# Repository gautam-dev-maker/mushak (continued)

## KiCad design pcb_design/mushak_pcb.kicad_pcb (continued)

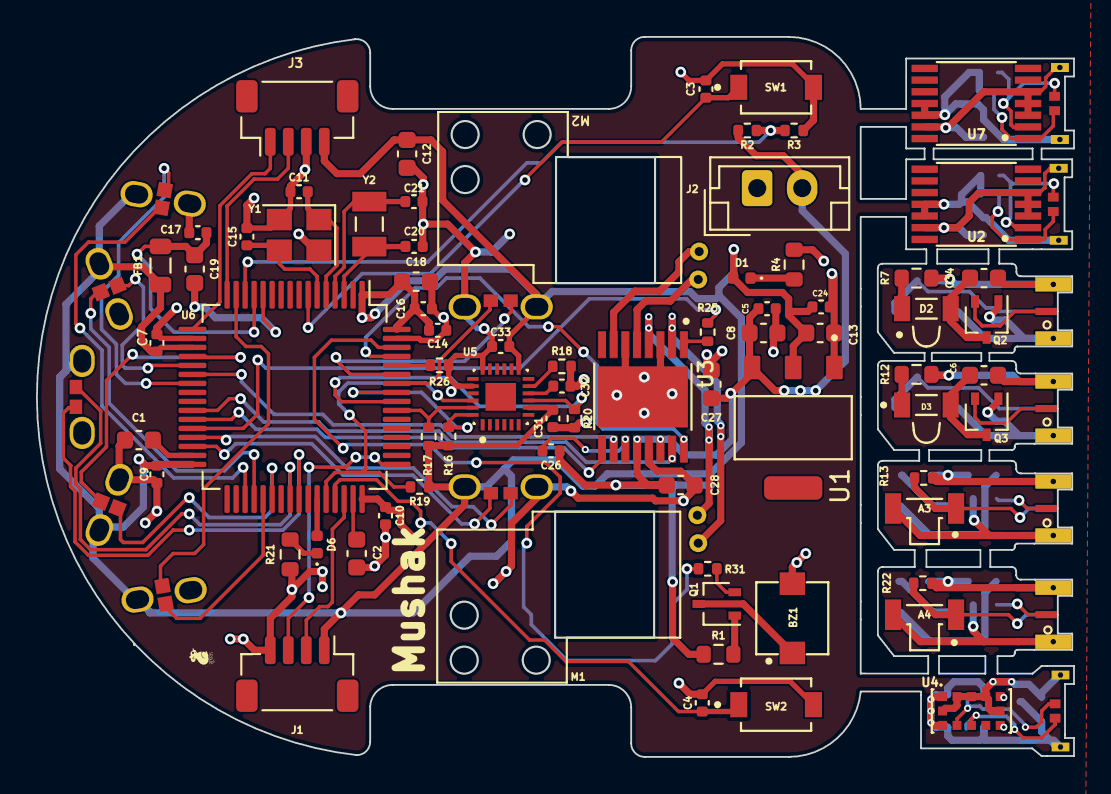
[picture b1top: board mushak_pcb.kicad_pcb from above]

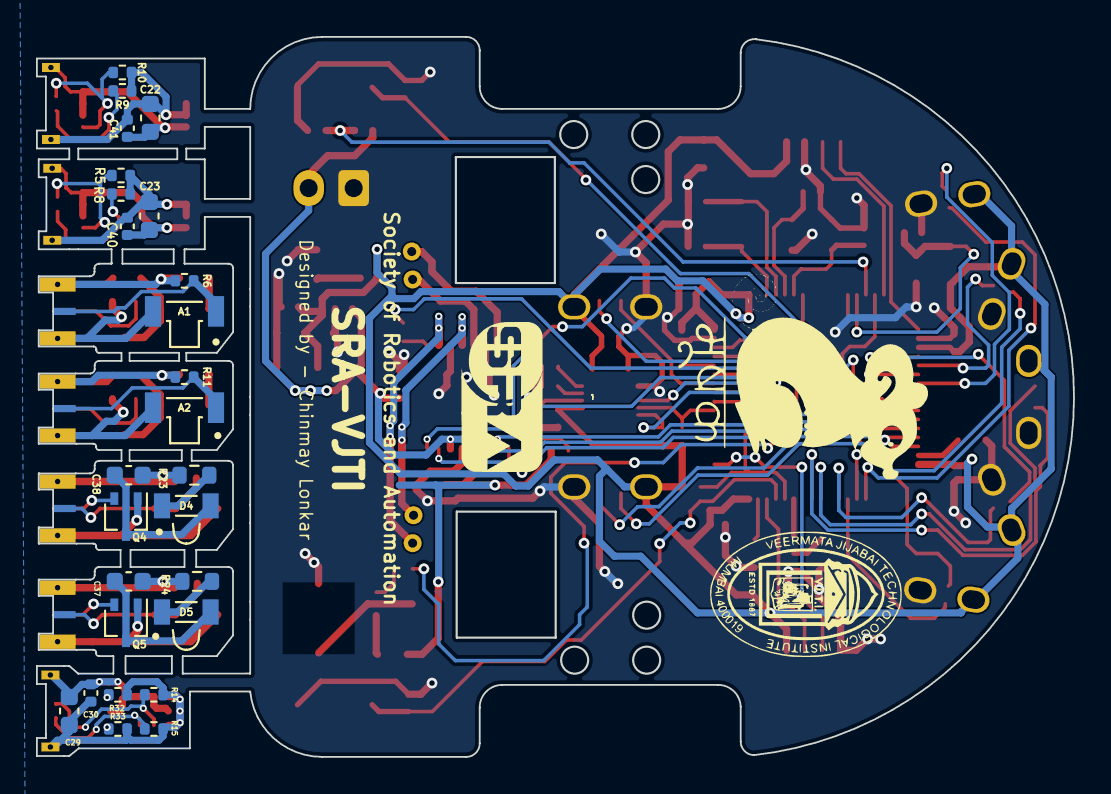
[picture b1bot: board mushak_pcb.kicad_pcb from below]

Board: 2 copper layers, 57.6 x 40.0 mm, 113 parts (27 on the bottom side), 94 nets.

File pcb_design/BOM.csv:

,,,,MUSHAK BILL OF MATERIALS,,,,,,,,,,,,
purchase later,,to purchase ,,,,,,,,,,,,,,
already purchased,,remove from module,,,,,,,,,,,,,,
,,,,,,,f,,,,,,,,,
Ref,Quantity,Value,Comp name,Footprint,Description,Vendor (Digikey),Vendor (Mouser),Indian Vendor (best price),Best Buy (₹ / piece) inc. GST,Cost per build (₹),Purchase Qty,Overall cost (₹) 40% off on Evelta for min. 10 piece,Comments,Cost per build ($),LCSC,Cost ($)
"A1, A2, A3, A4,",4,SFH_3015_FA,SFH_3015_FA,SFH_3015_FA:XDCR_SFH_3015_FA,IR_Reciever,SFH_3015_FA (₹49.86/10piece),SFH_3015_FA (₹40.86/10piece),Not available in India,59.93,239.72,10,498.58,Not available on Indian sites ( Already ordered from semikart),,out of stock,
"BZ1,",1,Buzzer,Buzzer,SMT-0440-T-R:XDCR_SMT-0440-T-R,"Buzzer, polarized",digikey,mouser,semikart(digikey),247.69,247.69,1,247.69,SMD version not available in India,,discontinued,
"C1, C2, C27,",3,2.2uF,C,Capacitor_SMD:C_0603_1608Metric,Unpolarized capacitor,2.2uF_0402 (₹18.46/10piece),2.2uF_0402 (₹11.69/10 piece),evelta,8.26,24.78,10,49.56,0603 package available,0.27,C417153,0.09
"C14, C22, C23,C3, C4, C5, C6, C7, C9, C10, C16, C30, C32, C33, C36, C37, C24, C25",18,0.1uF,C,Capacitor_SMD:C_0402_1005Metric,Unpolarized capacitor,0.1uF_0402 (₹2.32/10piece),0.1uF_0402 (₹3.34/10 piece),evelta,2.12,38.16,35,44.6,pack of 35,0,discontinued,
" C13,",1,22uF,C,Capacitor_SMD:C_0603_1608Metric,Unpolarized capacitor,,,ktron,1.42,1.42,15,21.24,,0,0402 not found,
"C11, C15,",2,20pF (22uF * avaiable),C,Capacitor_SMD:C_0402_1005Metric,Unpolarized capacitor,digikey,20 pF (12.41/10 piece),evelta,3.96,7.92,10,23.76,got 22pF instead of 20pF,0,discontinued,
"C12, C19, C34, C35, C38, C39,",6,1uF,C,Capacitor_SMD:C_0603_1608Metric,Unpolarized capacitor,digikey,mouser,ktron,1,6,20,12,got 0603 package,0.1878,C913450,0.0313
"C17,C31,C26,",3,0.01uF,C,Capacitor_SMD:C_0402_1005Metric,Unpolarized capacitor,digikey,mouser,evelta,0.59,1.77,10,3.54,,0,discontinued,
"C18, C28, C8, C23, C22",5,10uF,C,Capacitor_SMD:C_0603_1608Metric,Unpolarized capacitor,digikey,mouser,evelta,3.54,17.7,10,21.24,got 0603 package,0.556,C703695,0.1112
"C20, C21,",2,12.5pF,C,Capacitor_SMD:C_0402_1005Metric,Unpolarized capacitor,,,evelta,2.5,5,10,15,got 12 pF instead of 12.5pF,0,discontinued,
"C29,",1,4.7uF,C,Capacitor_SMD:C_0603_1608Metric,Unpolarized capacitor,digikey,mouser,evelta,4.72,4.72,10,28.32,got 0603 package,0,discontinued,
"D1, D6,",2,LED,LED,LED_SMD:LED_0402_1005Metric,Light emitting diode,--,--,evelta,3.1,6.2,10,48.97,other colours are cheaper but I went for green,0,,
"D2, D3, D4, D5,",4,SFH_4045N,SFH_4045N,SFH_4045N:LED_SFH_4045N,IR_transmitter,SFH_4045N (₹51.14),SFH_4045N (₹52.47),Not available in India,51.14,204.56,10,337.98,Not available on Indian sites (digikey) ( Already ordered from semikart),0,unavailable,
"FB1,",1,120R,FerriteBead_Small,Inductor_SMD:L_0805_2012Metric,"Ferrite bead, small symbol",,,evelta,2.11,2.11,10,12.66,I want to make sure if this component is correct,0,out of stock,
"IC1, IC2,",2,AS5048B-HTSP,AS5048B-HTSP,AS5048B-HTSP:SOP65P640X120-14N,Magnetic Encoder,digikey,,Not available in India,727.62,1455.24,2,1455.24,we have it already,0,out of stock,
"J1,",1,Conn_01x04_Male,Conn_01x04_Male,Connector_JST:JST_SH_BM04B-SRSS-TB_1x04-1MP_P1.00mm_Vertical,"Generic connector, single row, 01x04",,,evelta,11.8,11.8,0,0,Available in toyo connectors,0,,
"J2,",1,Conn_01x02_Female,Conn_01x02_Female,Connector_JST:JST_EH_B2B-EH-A_1x02_P2.50mm_Vertical,"Generic connector, single row, 01x02",--,--,--,--,--,0,0,Available in toyo connectors,--,--,--
"Q1, Q2, Q3, Q4, Q5,",5,DMN3065LW-7,Q_NMOS_DGS,Package_TO_SOT_SMD:SOT-323_SC-70,"N-MOSFET transistor, drain/gate/source",digikey,,semikart(digikey),42.893,42.893,12,514.72,,0,,
"R1,",1,10E,R,Resistor_SMD:R_0603_1608Metric,Resistor,10 ohm (₹2.4/10 piece),10 ohm (₹1.99/10 piece),evelta,1.89,1.89,5,5.67,,0.075,C153363,0.075
"R4,R21,",2,220E,R,Resistor_SMD:R_0603_1608Metric,Resistor,,,evelta,1.51,3.02,10,9.44,got 0402 package,0,unavailable,
"R5, R8, R9, R10, R14, R15,R2, R3,",8,4.7k,R,Resistor_SMD:R_0402_1005Metric,Resistor,,,evelta,0.47,3.76,20,5.64,got 0603 package,0.3312,C513719,0.0414
"R6, R11, R13, R16, R17, R18, R19, R20, R22, R26",10,10k,R,Resistor_SMD:R_0402_1005Metric,Resistor,,,evelta,1.18,11.8,25,17.7,got 0402 package,0,out of stock,
"R7, R12, R23, R24,",4,100E,R,Resistor_SMD:R_0603_1608Metric,Resistor,,,evelta,1.89,7.56,10,9.44,,0,unavailable,
"R27, R28, R29, R30, R31",5,150E,R,Resistor_SMD:R_0402_1005Metric,Resistor,,,evelta,12,60,10,120,,,,
"SW1, SW2,",2,SW_Push,SW_Push,TL1015AF160QG:SW_TL1015AF160QG,"Push button switch, generic, two pins",,,evelta,2.183,4.366,10,21.83,,0,discontinued,
"U2,",1,BA30BC0FP-E2,BA30BC0FP-E2,IPD50P04P4L-11:DPAK228P998X235-3N,1A 3V LDO,,,semikart(mouser),100.78,100.78,3,302.34,,0,out of stock,
"U3,",1,DRV8833PW,DRV8833PW,Package_SO:TSSOP-16_4.4x5mm_P0.65mm,"Dual H-Bridge Motor Driver, TSSOP-16",digikey,mouser,Not available in India,209.34,209.34,1,209.34,,3.4858,C50506,3.4858
"U4,",1,VL6180XV0NR/1,VL6180XV0NR{slash}1,VL6180XV0NR_1:LGA12R75P2X6_280X480X110,ToF,digikey,mouser,tanotis,648,648,1,648,,3.2063,C2688732,3.2063
"U5,",1,MPU-6500,MPU-6500,MPU-6500:QFN40P300X300X95-25N,IMU,digikey,mouser,Not available in India (from module),727.89,727.89,1,727.89,,3.5651,C50278,3.5651
"U6,",1,STM32F405RGTx,STM32F405RGTx,Package_QFP:LQFP-64_10x10mm_P0.5mm,"ARM Cortex-M4 MCU, 1024KB flash, 128KB RAM, 168MHz, 1.8-3.6V, 51 GPIO, LQFP-64",digikey,mouser,Not available in India,,0,,0,,10.1327,C15742,10.1327
"Y1,",1,25Mhz,Crystal_GND24,Crystal:Crystal_SMD_3225-4Pin_3.2x2.5mm,"Four pin crystal, GND on pins 2 and 4",,,electronicscomp,34.69,34.69,10,208.14,,0.8782,C295525,0.8782
"Y2,",1,32.768kHz,Crystal,ABS07-32:XTAL_ABS07-32.768KHZ-T,Two pin crystal,assign footprint,,evelta,9.44,9.44,3,28.32,,0.1737,C93228,0.1737
Number of SMD components = ,101,,,,,,,,,,,,,,,
,,,,,,,,,,,TOTAL,5648.85,,,,
,98,,,,,,,,,,,,,,,

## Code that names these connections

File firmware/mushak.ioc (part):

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Mcu.Name=STM32F405RGTx
Mcu.Package=LQFP64
Mcu.UserName=STM32F405RGTx
PA0-WKUP.Signal=ADCx_IN0
PA1.Signal=ADCx_IN1
PA10.GPIOParameters=GPIO_Label
PA10.GPIO_Label=DEBUG_LED
PA10.Signal=GPIO_Output
PA11.GPIOParameters=PinState,GPIO_Label
PA11.GPIO_Label=MPU6500_CS
PA11.PinState=GPIO_PIN_RESET
PA11.Signal=GPIO_Output
PA12.GPIOParameters=GPIO_Label
PA12.GPIO_Label=DEBUG_BTN
PA12.Signal=GPIO_Input
PA13.Mode=Serial_Wire
PA13.Signal=SYS_JTMS-SWDIO
PA14.Mode=Serial_Wire
PA14.Signal=SYS_JTCK-SWCLK
PA2.Mode=Asynchronous
PA2.Signal=USART2_TX
PA3.Mode=Asynchronous
PA3.Signal=USART2_RX
PA4.Signal=ADCx_IN4
PA5.Signal=ADCx_IN5
PA6.Signal=S_TIM13_CH1
PA7.Signal=ADCx_IN7
PA8.Mode=I2C
PA8.Signal=I2C3_SCL
PB0.Signal=S_TIM3_CH3
PB1.Signal=S_TIM3_CH4
PB10.Mode=I2C
PB10.Signal=I2C2_SCL
PB11.Mode=I2C
PB11.Signal=I2C2_SDA
PB14.Signal=S_TIM12_CH1
PB15.Signal=S_TIM12_CH2
PB2.GPIOParameters=GPIO_Speed,GPIO_Label
PB2.GPIO_Label=DRV8833_EN
PB2.GPIO_Speed=GPIO_SPEED_FREQ_HIGH
PB2.Signal=GPIO_Output
PB3.Mode=Full_Duplex_Master
PB3.Signal=SPI1_SCK
PB4.Mode=Full_Duplex_Master
PB4.Signal=SPI1_MISO
PB5.Mode=Full_Duplex_Master
PB5.Signal=SPI1_MOSI
PB6.Mode=I2C
PB6.Signal=I2C1_SCL
PB7.Mode=I2C
PB7.Signal=I2C1_SDA
PB8.Signal=S_TIM10_CH1
PB9.Signal=S_TIM11_CH1
PC14-OSC32_IN.Mode=LSE-External-Oscillator
PC14-OSC32_IN.Signal=RCC_OSC32_IN
PC15-OSC32_OUT.Mode=LSE-External-Oscillator
PC15-OSC32_OUT.Signal=RCC_OSC32_OUT
PC6.Signal=S_TIM3_CH1
PC7.Signal=S_TIM3_CH2
PC9.Mode=I2C
PC9.Signal=I2C3_SDA
PH0-OSC_IN.Mode=HSE-External-Oscillator
PH0-OSC_IN.Signal=RCC_OSC_IN
PH1-OSC_OUT.Mode=HSE-External-Oscillator
PH1-OSC_OUT.Signal=RCC_OSC_OUT
RCC.HSE_VALUE=25000000
RCC.SYSCLKFreq_VALUE=168000000
RCC.SYSCLKSource=RCC_SYSCLKSOURCE_PLLCLK
board=custom

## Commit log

2022-07-05 Add gitignore file
2022-07-19 Add BLE logging support
2022-07-19 Add functionality to choose USART instance in BLE logging library
2022-07-19 Add I2C library and VL6180x driver
2022-07-19 Add AS5600 driver
2022-07-20 Correct the typo of i2c in Makefile
2022-07-20 Solve I2C_Handler bug
2022-08-01 vl6180x tested
2022-08-05 update VL6180x driver
2022-08-07 Update VL6180x to give correct readings
2022-08-09 Add MPU6500 driver
2022-08-09 Add schematics
2022-08-09 Add footprints
2022-08-11 Update Schematics and footprints for sensors
2022-08-11 updated .gitignore
2022-08-12 Add Schematic for stm32F405
2022-08-13 Added CAD Files
2022-08-14 changed footprints of capacitors and resistors
2022-08-15 Add DRV8833 driver api
2022-08-15 made draft pcb footprint placement
2022-08-15 Add 3d models to footprint
2022-08-19 updated footprint for motors
2022-08-20 corrected encoder and motor driver schematics
2022-08-20 VL6180x part routed
2022-08-23 changed footprint of passive components
2022-08-23 Started Poer trace routing
2022-08-24 completed routing
2022-08-25 Completed sensor routing
2022-08-26 modified pcb outline and graphics
2022-08-26 modified graphics
2022-08-28 Added the New Mounts
2022-08-28 Updated graphics and added dimensions
2022-08-28 Update README.md to include the firmware part
2022-08-28 PCB Design for Mushak (#2)
    * Add Schematic for stm32F405
    * changed footprints of capacitors and resistors
    * made draft pcb footprint placement
    * Add 3d models to footprint
    * updated footprint for motors
    * corrected encoder and motor driver schematics
2022-08-28 Add PCB images
2022-08-28 Added assets folder for CAD design
2022-08-28 Update README.md
    Created Readme for CAD model
2022-08-29 Add File structure in README.md
2022-08-29 changed oscilattor placement
2022-08-29 Add files via upload
    Added final bot assembly pic
2022-08-29 Update README.md
    Added info to description of parts and final assembly pic
2022-08-29 Add readme and change sensor angles
2022-08-29 Add README for PCB Design
2022-08-29 CHanged angles for IR Sensor placement
2022-08-29 PCB_Readme (#3)
    * Add readme and change sensor angles
    * Add README for PCB Design
    * CHanged angles for IR Sensor placement
2022-08-29 Added New PCB Assembly
2022-08-30 Add images
2022-08-30 renamed folder and add pcb images
2022-08-30 deleted extra folder
2022-08-30 Edited CAD Readme
2022-08-30 correct path for images in README
2022-08-30 Fixed Image issues in ReadME
2022-08-30 Bold the communication protocol in README.md
2022-08-30 Added CAD Design
2022-08-30 Add the CAD Design in README.md
2022-08-30 Improved File Structure
2022-08-30 PCB Design Readme (#4)
    Update PCB Readme.md
2022-08-30 Add gerbers
2022-08-30 add graphiccs on PCB
2022-08-30 Update the pcb notation image
2022-08-30 Correct the discrepancies in README.md
2022-08-30 Add "About the project" above the "Table of Content"
2022-08-31 Add IR placement logic
2022-08-31 Correct IR placement image
2022-08-31 Add schematics pdf to pcb_design folder
2022-09-02 Add BOM to pcb_design
2022-09-14 Add "-u_printf_float" flag in linker script
    This commit solves the floating point issue in BLE_Logger.
    The flag was required to be added as the way to enable FPU for
    complex floating point processing.
2022-09-15 Remove ".lib" from .gitignore
2022-09-15 changed AS5600 to AS5048B
2022-09-15 change capacitor silkscreen placement
2022-09-18 modified capacitors for encoders
2022-09-18 update gerbers
2022-09-22 Data fusion with complementary filter
2022-09-29 Add resistors between MOSFET gate
2022-09-30 resolved routing errors
2022-09-30 updated BoM
2022-10-11 Correct BoM and placement files
2022-10-11 update schematics pdf
2022-10-12 enlarge PCB hole size
2022-10-12 Update placement files
2022-10-15 Update PCB as per manufacturing requirements
2022-10-15 modify silkscreen
2022-10-17 Updated PCB with HTSSOP16 package for DRV8833
2022-10-17 updated renders
2022-10-17 Update schematic
2022-10-17 Update PCB renders
2022-10-17 Modified Via Placement
2022-11-02 Add ADC support and example
2023-03-01 Update mushak PCB with new changes * Add AMS1117 as 3.3v regulator * Add new alternate placement for IR sensors * Add new 3.3v compatible ToF sensor * Update gerber files
2023-03-12 Add changes to silkscreen and filter capacitors
2023-04-07 Update Mushak PCB design to include new features (#5)
    * Update mushak PCB with new changes
    * Add AMS1117 as 3.3v regulator
    * Add new alternate placement for IR sensors
    * Add new 3.3v compatible ToF sensor
    * Update gerber files
    * Add changes to silkscreen and filter capacitors
2023-10-09 Add logging driver library with arm semihosting support
2023-10-14 Add pwm and drv88333 driver
2023-10-14 Add Driver for ADC
    * Add api to access IR sensor
    * Add api for reading battery voltage
